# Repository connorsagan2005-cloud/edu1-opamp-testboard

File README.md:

# EDU1 MQP — chip characterization & datasheet

Top-level repository for the WPI Major Qualifying Project characterizing the **EDU1**
mixed-signal IC (reported name **CRIMSON**). The chip was designed and taped out by a
prior team; this project develops the test procedures, characterizes each analog block
on custom PCBs, and produces the chip's first datasheet from measured results.

- **Team:** Connor, James, Matthew
- **Advisor:** Prof. Suat Ay · **TA:** Ibrahim Bozyel

## The chip

64 pins, ~12 independent analog/digital blocks (2× VDAC, 2× IDAC, 4-channel ADC,
2× instrumentation amp, 2× op-amp, 2× comparator, 2× 555-style timer, 2× LDO,
1× bandgap reference), all configured over a 5-pin serial scan chain
(`sin` / `sclk` / `srstb` / `slatch` / `ssel`).

**This term's scope:** bandgap reference (BGR), LDO, comparator, op-amp.
Everything else (VDAC / IDAC / ADC / instrumentation amps / timers) is next term, on
separate PCBs.

## Architecture: master board + portable hierarchical blocks

This is a **monorepo** (not submodules — the master project and the blocks reference
each other by relative KiCad sheet paths, which submodules make painful).

- **One master board project owns the chip.** It carries the `DUT` symbol for the EDU1
  padframe, the main VAA bench connector + current-insertion jumper, the scan/control
  header, and the single AGND/DGND ground tie point. Owned by a groupmate; lives in
  [`hardware/master-board/`](hardware/master-board/).
- **Each analog block is its own self-contained, portable KiCad hierarchical block**
  under [`hardware/blocks/`](hardware/blocks/), exposing a small set of named external
  pins (e.g. `vaa`, `agnd`, plus the block's signal pins). No `DUT` symbol inside a
  block, no duplicated board-wide infrastructure.
- **Integration** = place the block as a hierarchical sheet in the master project and
  wire its exposed pins to the `DUT` symbol by hand.

Why: portability (a block can be opened, edited and verified standalone) and a single
shared DUT / power / scan infrastructure instead of a copy per block.

The op-amp block ([`hardware/blocks/opamp/`](hardware/blocks/opamp/)) is complete and
is the **reference example** — its README's integration section is the worked
procedure every future block should follow.

## Net-naming convention

- **Chip pin names** stay exactly as the padframe / pinout spreadsheet and the shared
  `EDU1` KiCad symbol define them. That is the source of truth — never renamed per
  block.
- **Board-wide global nets** (chip supply / ground) get UPPERCASE names defined once:
  `vaa` → `VAA`, `agnd` → `AGND`, etc.
- **`REF`** (the vaa/2 pseudo-ground) is reserved globally. Reuse it exactly; never
  redefine it in a new block.
- **Block-local nets** get a `<BLOCK><CHANNEL>_<FIXTURE>_` prefix, e.g. `CH1_A_INN`
  for op-amp channel 1, fixture A. Future blocks follow the same pattern:
  `COMP1_...`, `BGR_...`, `LDO_...`.

## Directory map

```
docs/
  chip/            EDU1 pinout spreadsheet, shared EDU1.kicad_sym + changelog, pin notes
  standards/       INDEX.md only — links each block to its test-template standard/datasheet
                   (no copyrighted PDFs in git)
  test-procedures/ one subfolder per block: finalized test-circuit spec + deviations doc
  meeting-notes/
hardware/
  master-board/    groupmate's project: DUT symbol, VAA connector + current jumper,
                   scan header, AGND/DGND tie  (README stub for now)
  blocks/
    opamp/         complete — reference example
    comparator/    not started (stub)
    bandgap-ref/   not started (stub)
    ldo/           not started (stub)
  shared-libs/     symbol/footprint libraries shared across blocks + master
firmware/          FPGA (Basys 3) scan-chain driver / test automation  (stub)
test-scripts/      bench automation / data capture / per-block analysis  (stub)
results/           measured characterization data → datasheet source  (stub)
```

## How to add a new block

Derived from how the op-amp block was built and integrated:

1. **Make a folder** under `hardware/blocks/<block>/` with its own `.kicad_pro` and
   schematic set. No `DUT` symbol, no board-wide power/scan/ground infrastructure —
   the master board owns all of that.
2. **Define the external interface** as a small set of hierarchical labels on the top
   sheet: `vaa`, `agnd`, plus the block's chip-facing signal pins named exactly as the
   EDU1 symbol names them. Reuse `REF` as-is if the block needs the vaa/2 pseudo-ground;
   never redefine it.
3. **Keep block-local nets prefixed** `<BLOCK><CHANNEL>_<FIXTURE>_` (see convention
   above).
4. **Bundle the generic symbol libs** you use plus a local `sym-lib-table` with
   `${KIPRJMOD}` URIs so the project opens standalone. The corrected `EDU1.kicad_sym`
   comes from `hardware/shared-libs/`, not a per-block copy.
5. **Verify standalone:** export an XML netlist with `kicad-cli`, check it against the
   spec, run ERC, and record results under `verification/`. Document any ERC findings
   you are deliberately not suppressing.
6. **Integrate:** in the master project, place the block as a hierarchical sheet
   pointing at `../blocks/<block>/<block>.kicad_sch`, import its sheet pins, and wire
   them to the `DUT` symbol and analog rails by hand.
7. **Write the block README** with an integration table (border pin → internal net →
   master connection), following `hardware/blocks/opamp/README.md`.

## Branch convention

One feature branch per block/person, merged into the default branch via PR, so the
master-board owner and each block owner aren't editing the same schematic files
directly.

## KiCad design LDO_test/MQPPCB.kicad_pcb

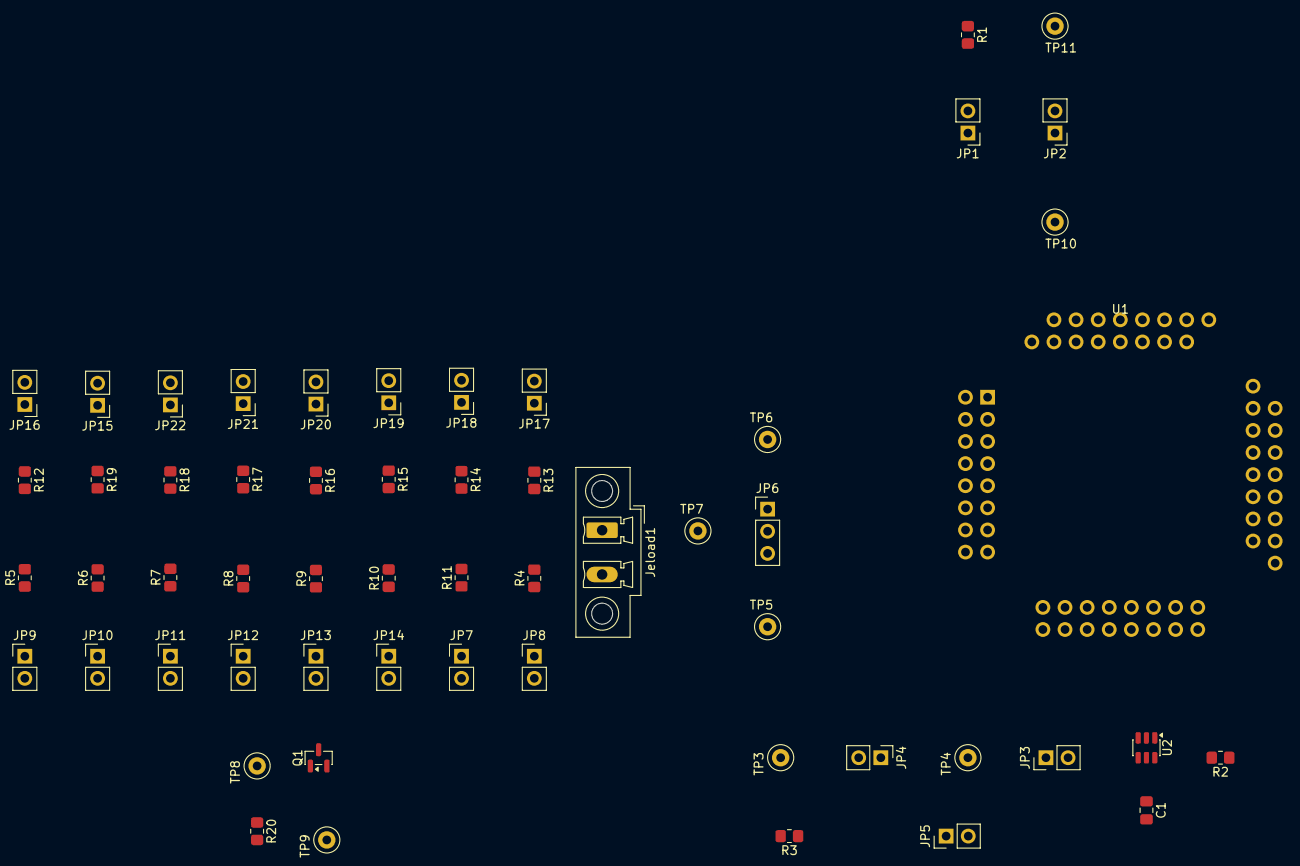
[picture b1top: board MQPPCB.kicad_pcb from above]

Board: 4 copper layers, 56 parts (0 on the bottom side), 30 nets, no tracks yet.

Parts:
C1: 0.1uF; C_0805_2012Metric_Pad1.18x1.45mm_HandSolder
JP1, JP2, JP3, JP4, JP5, JP7, JP8, JP9, JP10, JP11, JP12, JP13, JP14, JP15, JP16, JP17, JP18, JP19, JP20, JP21, JP22: Jumper_2_Open; PinHeader_1x02_P2.54mm_Vertical
JP6: Jumper_3_Open; PinHeader_1x03_P2.54mm_Vertical
Jeload1: Conn_01x02_Pin; PhoenixContact_MCV_1,5_2-GF-5.08_1x02_P5.08mm_Vertical_Thre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
Q1: AO3400A; SOT-23
R1: 1k; R_0805_2012Metric_Pad1.20x1.40mm_HandSolder
R2, R20: 100k; R_0805_2012Metric_Pad1.20x1.40mm_HandSolder
R3, R5, R13: 180; R_0805_2012Metric_Pad1.20x1.40mm_HandSolder
R4, R12: 1.8k; R_0805_2012Metric_Pad1.20x1.40mm_HandSolder
R6, R14: 360; R_0805_2012Metric_Pad1.20x1.40mm_HandSolder
R7, R15: 510; R_0805_2012Metric_Pad1.20x1.40mm_HandSolder
R8, R16: 680; R_0805_2012Metric_Pad1.20x1.40mm_HandSolder
R9, R17: 910; R_0805_2012Metric_Pad1.20x1.40mm_HandSolder
R10, R18: 1.2k; R_0805_2012Metric_Pad1.20x1.40mm_HandSolder
R11, R19: 1.5k; R_0805_2012Metric_Pad1.20x1.40mm_HandSolder
TP3, TP4, TP5, TP6, TP7, TP8, TP9, TP10, TP11: TestPoint; TestPoint_Loop_D2.50mm_Drill1.0mm
U1: xxxxxxxxxxxxxxx; EDU1_DUT_Socket_PGA64_PCB3006-1
U2: TS5A3159ADBVR; SOT-23-6

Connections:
/LDOloadtest/STEP_CTRL: Q1.1 (G), R20.1, TP8.1 (1_1)
/LDOloadtest/ldo_out1: JP6.3 (B), TP5.1 (1_1), U1.15 (ldo_out1)
/LDOloadtest/ldo_out2: JP6.1 (A), TP6.1 (1_1), U1.14 (ldo_out2)
/VBAT_test/MUXctrl: R2.2, U2.6
/VBAT_test/Vbat: JP3.1 (A), JP3.2 (B), JP4.1 (A), JP5.2 (B), TP4.1 (1_1), U1.16 (vbat), U2.4
/VBAT_test/Vbatsrc: JP4.2 (B), R3.2, TP3.1 (1_1)
/VBAT_test/Vin_5V: C1.1, U2.5 (V+)
/V_enDC: JP2.2 (B), R1.1, TP11.1 (1_1)
GNDA: C1.2, JP15.2 (B), JP16.2 (B), JP17.2 (B), JP18.2 (B), JP19.2 (B), JP20.2 (B), JP21.2 (B), JP22.2 (B), Jeload1.2, Q1.2 (S), R2.1, R20.2, TP9.1 (1_1), U1.41 (agnd), U2.2 (GND)
unnamed: JP1.1 (A), JP2.1 (A), TP10.1 (1_1), U1.62 (power_en)
unnamed: JP1.2 (B), R1.2
unnamed: JP5.1 (A), R3.1
unnamed: JP6.2 (C), Jeload1.1, R4.2, R5.2, R6.2, R7.2, R8.2, R9.2, R10.2, R11.2, R12.2, R13.2, R14.2, R15.2, R16.2, R17.2, R18.2, R19.2, TP7.1 (1_1)
unnamed: JP7.1 (A), R11.1
unnamed: JP8.1 (A), R4.1
unnamed: JP9.1 (A), R5.1
unnamed: JP10.1 (A), R6.1
unnamed: JP7.2 (B), JP8.2 (B), JP9.2 (B), JP10.2 (B), JP11.2 (B), JP12.2 (B), JP13.2 (B), JP14.2 (B), Q1.3 (D)
unnamed: JP11.1 (A), R7.1
unnamed: JP12.1 (A), R8.1
unnamed: JP13.1 (A), R9.1
unnamed: JP14.1 (A), R10.1
unnamed: JP15.1 (A), R19.1
unnamed: JP16.1 (A), R12.1
unnamed: JP17.1 (A), R13.1
unnamed: JP18.1 (A), R14.1
unnamed: JP19.1 (A), R15.1
unnamed: JP20.1 (A), R16.1
unnamed: JP21.1 (A), R17.1
unnamed: JP22.1 (A), R18.1
